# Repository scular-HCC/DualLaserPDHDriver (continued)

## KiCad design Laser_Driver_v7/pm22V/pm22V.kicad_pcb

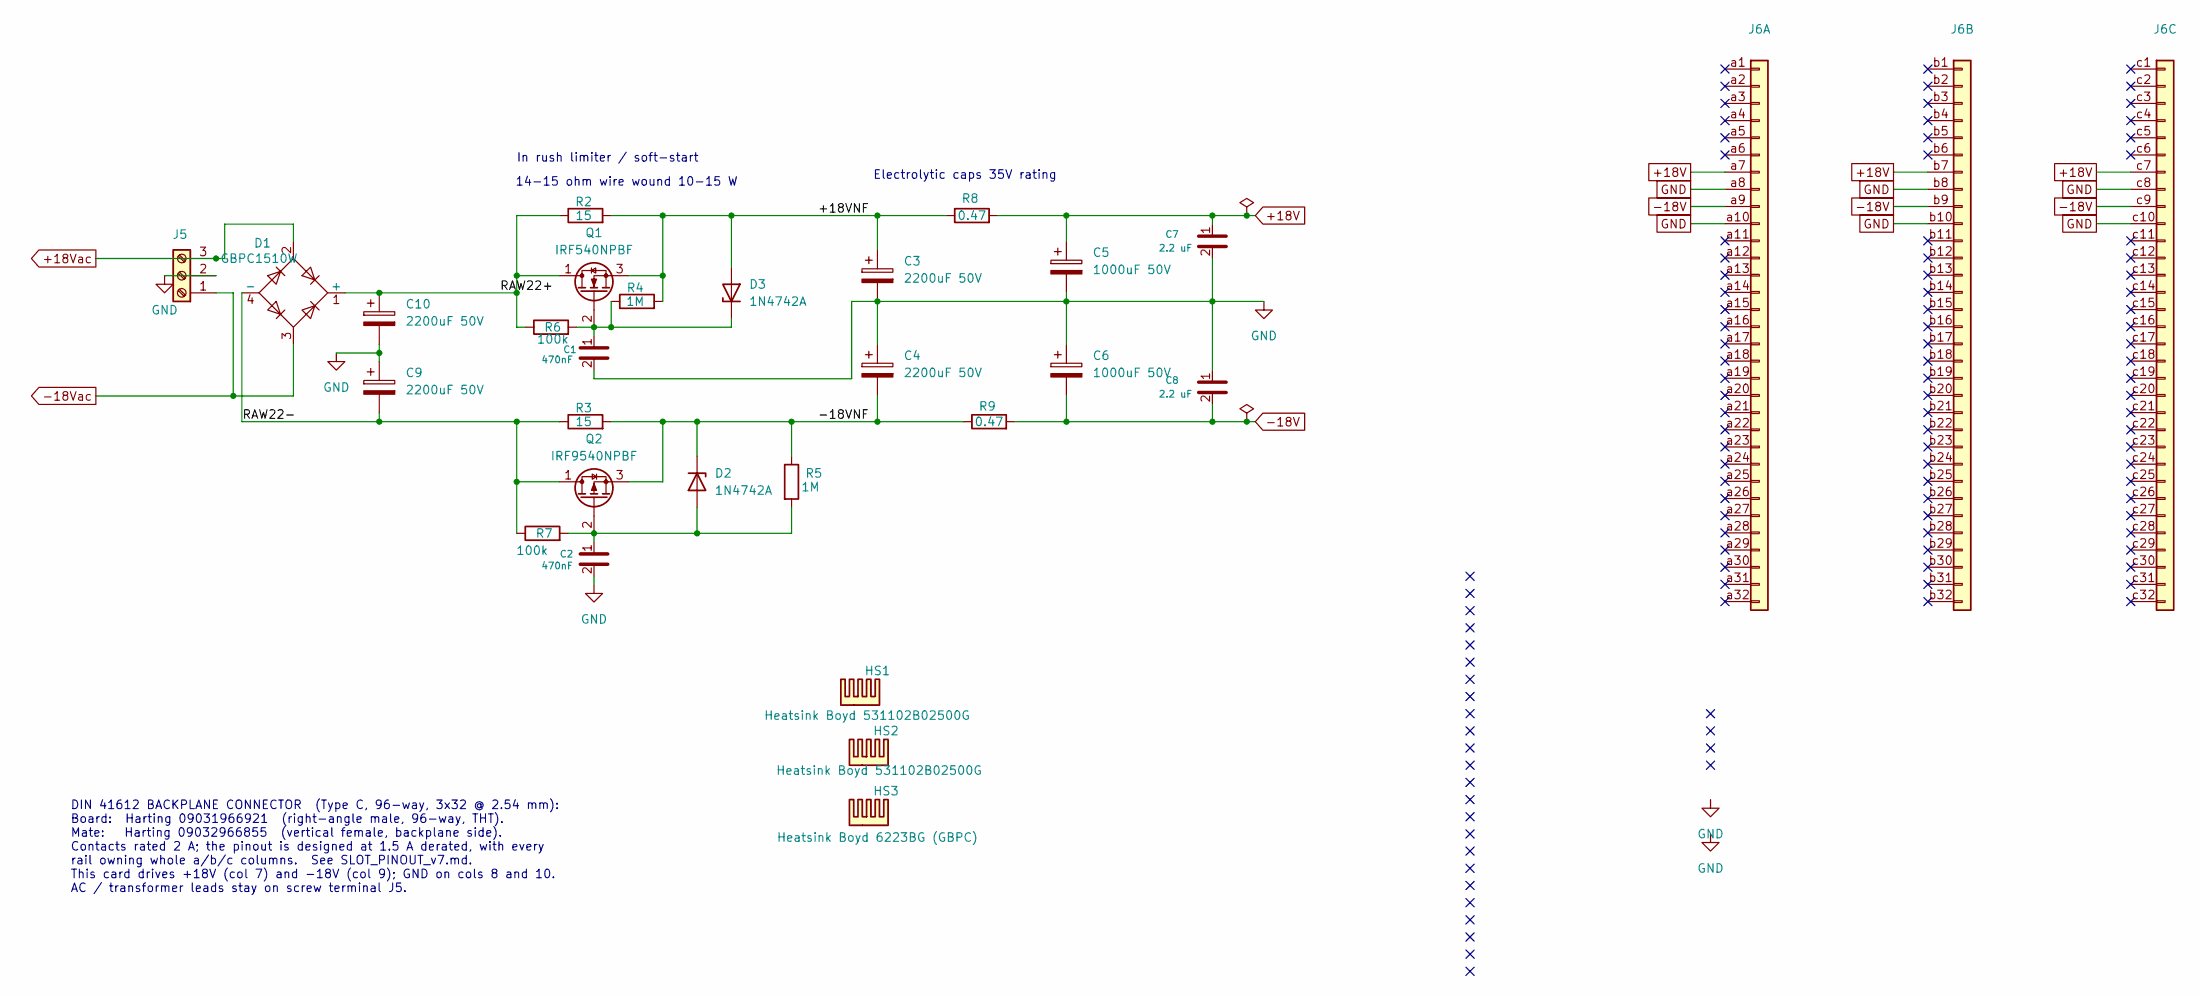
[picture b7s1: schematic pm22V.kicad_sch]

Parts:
C1, C2: 470nF; C_0805_2012Metric_Pad1.18x1.45mm_HandSolder
C3, C4, C9, C10: 2200uF 50V; CP_Radial_D18.0mm_P7.50mm
C5, C6: 1000uF 50V; CP_Radial_D16.0mm_P7.50mm
C7, C8: 2.2 uF; C_0805_2012Metric_Pad1.18x1.45mm_HandSolder
D1: GBPC1510W; Diode_Bridge_28.6x28.6x7.3mm_P18.0mm_P11.6mm; Manufacturer Part Number GBPC1510W; DigiKey P/N 2616-GBPC1510W-ND
D2, D3: 1N4742A; D_DO-41_SOD81_P10.16mm_Horizontal
HS1, HS2: Heatsink Boyd 531102B02500G; Heatsink_AAVID_Extruded_531102B02500G_34.9x12.7mm_H38.1mm
HS3: Heatsink Boyd 6223BG (GBPC); Bridge_GBPC_Heatsink_Boyd_6223BG
J5: Screw_Terminal_01x03; TerminalBlock_Phoenix_MKDS-1,5-3-5.08_1x03_P5.08mm_Horizont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; MPN 1729131
J6: DIN41612_03x32_C_Split; DIN41612_C_3x32_Male_Horizontal_THT
Q1: IRF540NPBF; TO-220-3_Vertical
Q2: IRF9540NPBF; TO-220-3_Vertical
R2, R3: 15; R_Axial_Power_L38.0mm_W9.0mm_P45.72mm
R4, R5: 1M; R_0805_2012Metric_Pad1.20x1.40mm_HandSolder
R6, R7: 100k; R_0805_2012Metric_Pad1.20x1.40mm_HandSolder
R8, R9: 0.47; R_1206_3216Metric_Pad1.30x1.75mm_HandSolder; MPN CRL1206-FW-R470ELF

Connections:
+18V: C5.1, C7.1, J6.a7, J6.b7, J6.c7, R8.2
+18Vac: D1.2, J5.3
-18V: C6.2, C8.2, J6.a9, J6.b9, J6.c9, R9.2
-18Vac: D1.3, J5.1
/+18VNF: C3.1, D3.2 (A), Q1.3 (S), R2.2, R4.2, R8.1
/-18VNF: C4.2, D2.1 (K), Q2.3 (S), R3.2, R5.1, R9.1
/RAW22+: C10.1, D1.1 (+), Q1.1 (D), R2.1, R6.1
/RAW22-: C9.2, D1.4 (-), Q2.1 (D), R3.1, R7.1
GND: C1.2, C2.2, C3.2, C4.1, C5.2, C6.1, C7.2, C8.1, C9.1, C10.2, J5.2, J6.a8, J6.a10, J6.b8, J6.b10, J6.c8, J6.c10
unnamed: C2.1, D2.2 (A), Q2.2 (G), R5.2, R7.2
unnamed: C1.1, D3.1 (K), Q1.2 (G), R4.1, R6.2

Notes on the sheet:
Electrolytic caps 35V rating
DIN 41612 BACKPLANE CONNECTOR (Type C, 96-way, 3x32 @ 2.54 mm): Board: Harting 09031966921 (right-angle male, 96-way, THT). Mate: Harting 09032966855 (vertical female, backplane side). Contacts rated 2 A; the pinout is designed at 1.5 A derated, with every rail owning whole a/b/c columns. See SLOT_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
In rush limiter / soft-start
14-15 ohm wire wound 10-15 W

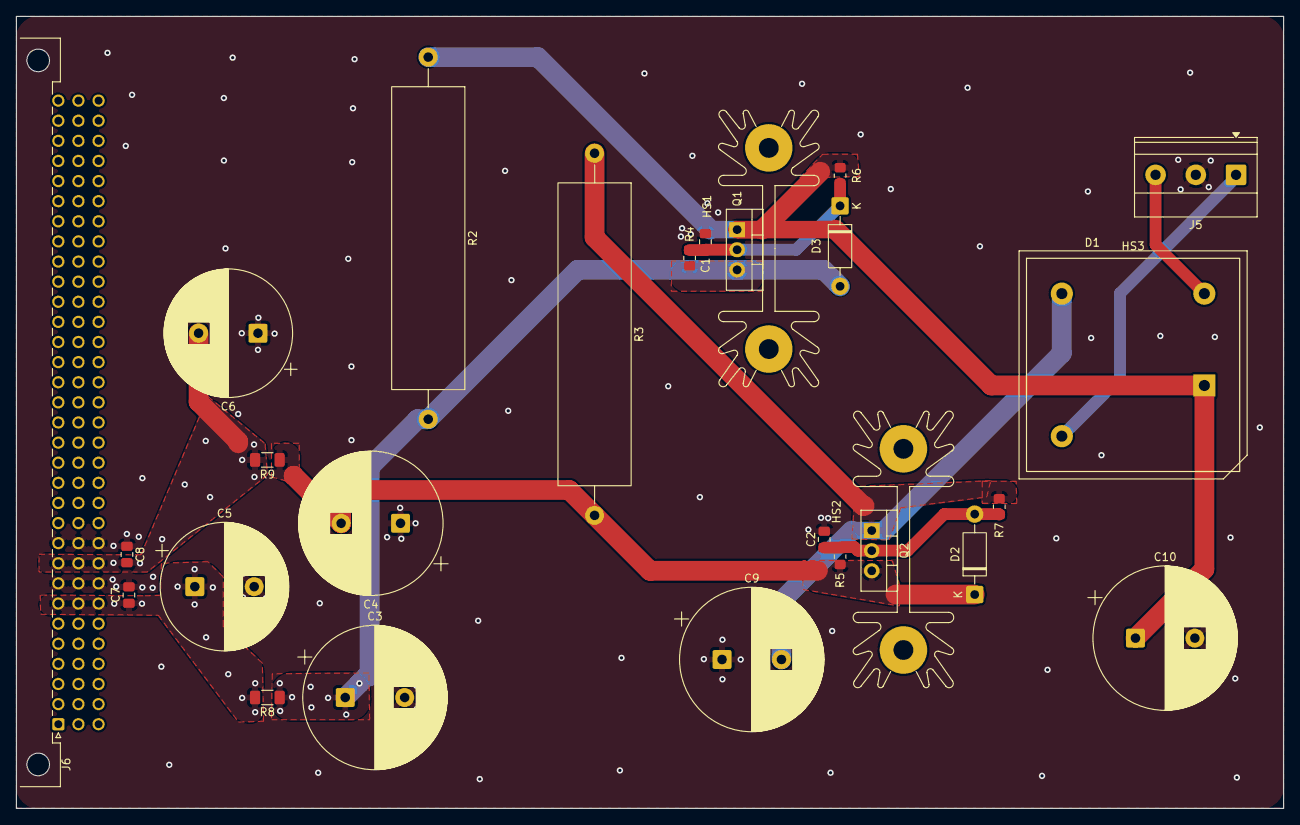
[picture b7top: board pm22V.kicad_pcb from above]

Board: 2 copper layers, 160.0 x 100.0 mm, 28 parts (0 on the bottom side), 11 nets.

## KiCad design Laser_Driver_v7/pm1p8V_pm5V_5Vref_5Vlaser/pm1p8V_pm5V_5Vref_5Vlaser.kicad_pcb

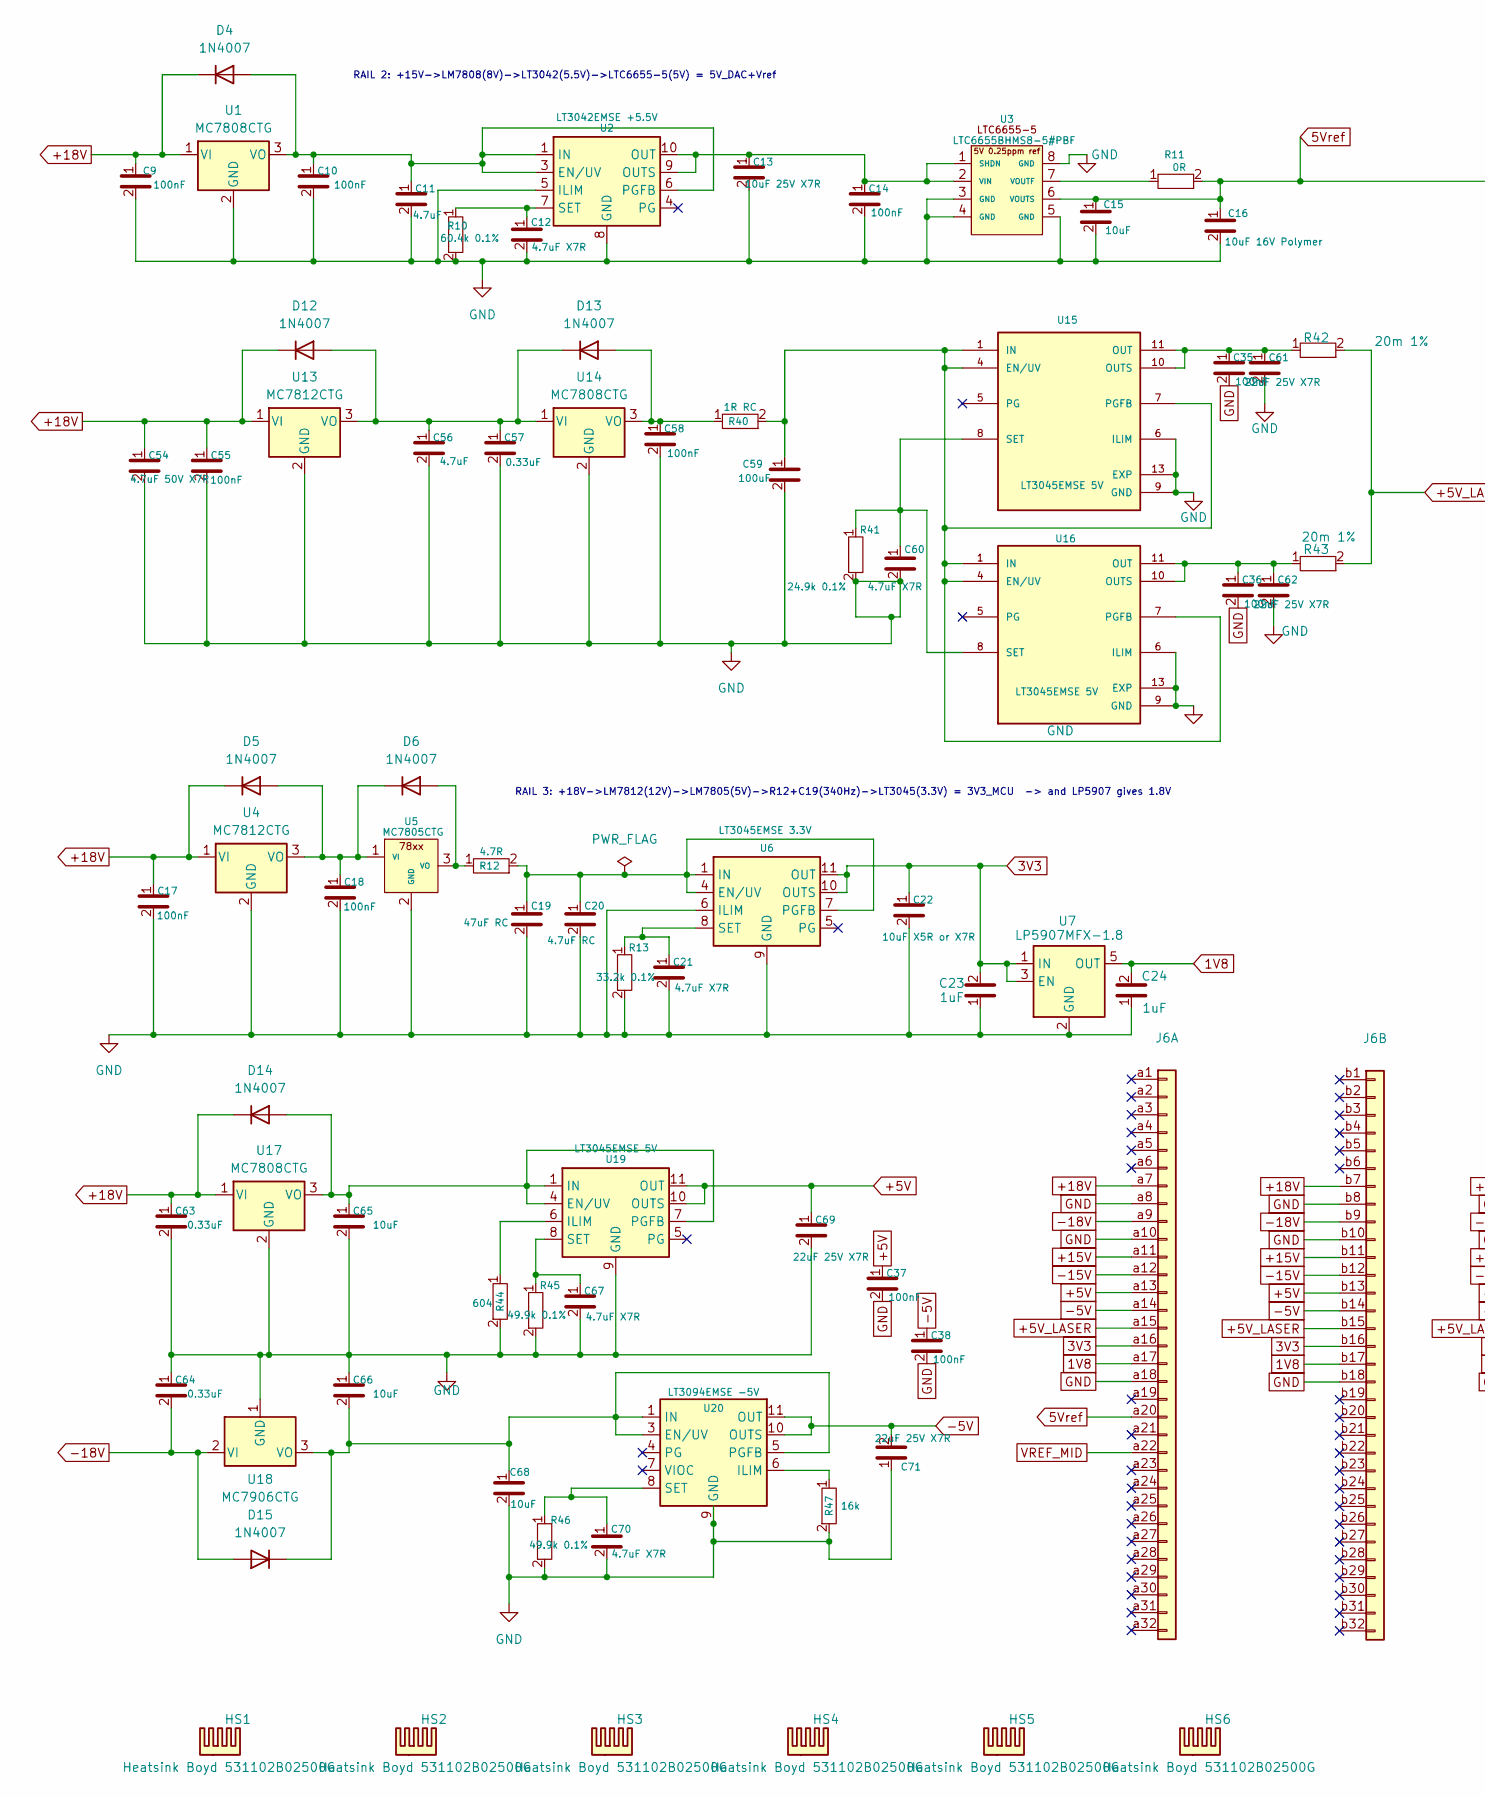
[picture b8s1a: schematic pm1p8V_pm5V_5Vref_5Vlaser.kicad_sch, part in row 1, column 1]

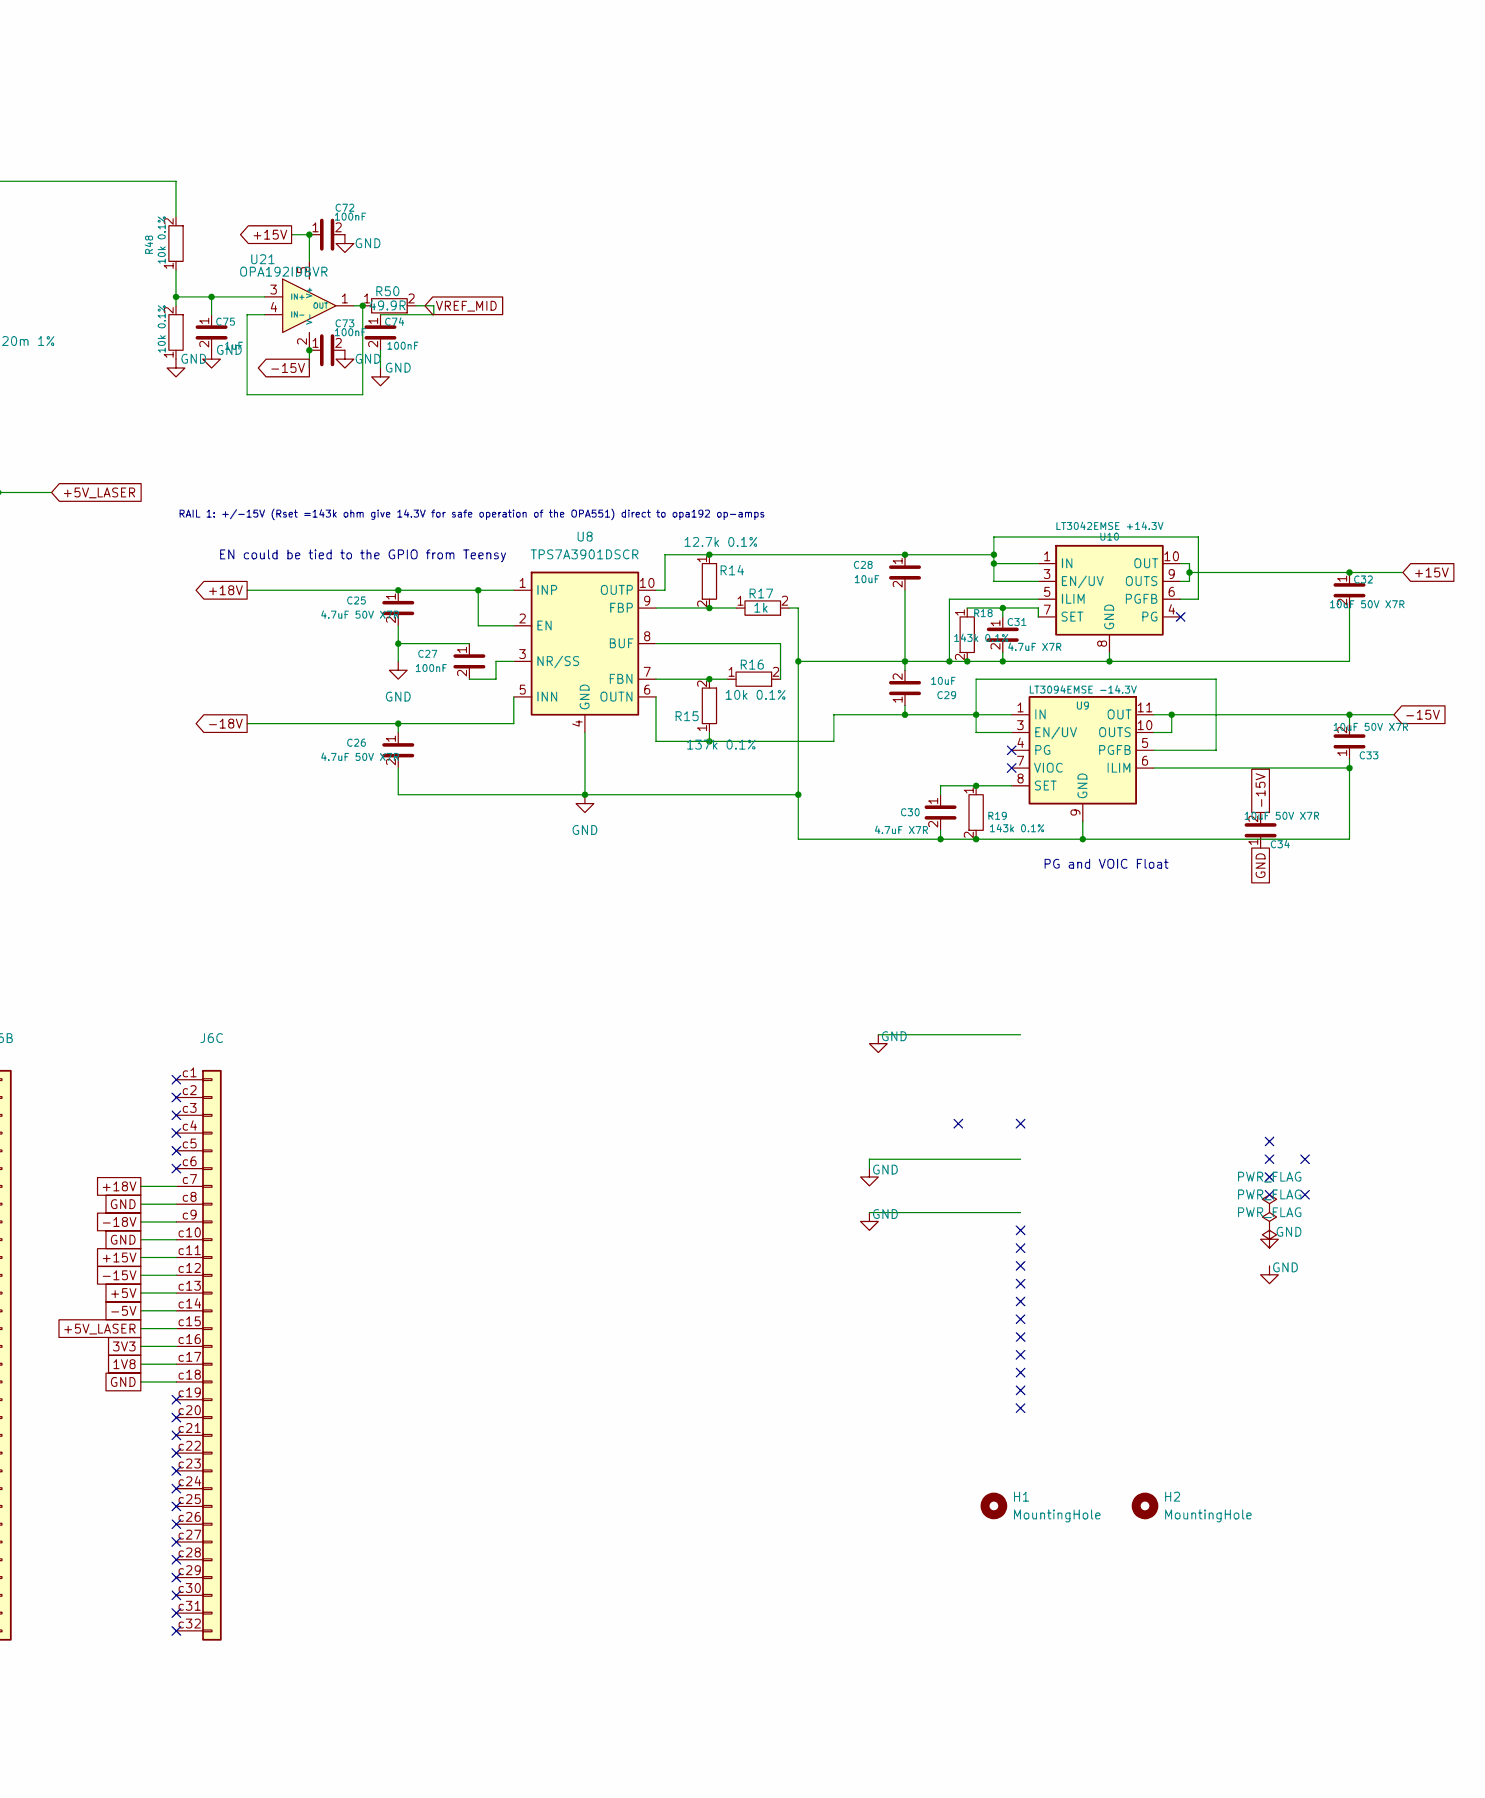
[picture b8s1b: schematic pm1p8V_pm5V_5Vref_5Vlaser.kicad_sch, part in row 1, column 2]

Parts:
C9, C10, C14, C17, C18, C27, C35, C36, C37, C38, C55, C58, C72, C73, C74: 100nF; C_0805_2012Metric_Pad1.18x1.45mm_HandSolder; Manufacturer Part Number CL21B104KBCNNNC; DigiKey P/N 1276-1003-2-ND
C11, C56: 4.7uF; C_0805_2012Metric_Pad1.18x1.45mm_HandSolder; Manufacturer Part Number CL21B475KAFNNNE; DigiKey P/N 1276-2969-2-ND
C12, C21, C30, C31, C60, C67, C70: 4.7uF X7R; C_0805_2012Metric_Pad1.18x1.45mm_HandSolder; Manufacturer Part Number CL21B475KAFNNNE; DigiKey P/N 1276-2969-2-ND
C13: 10uF 25V X7R; C_1206_3216Metric_Pad1.33x1.80mm_HandSolder; Manufacturer Part Number C1206C106K3RACTU; DigiKey P/N 399-C1206C106K3RACTUCT-ND
C15, C28, C29, C65, C66, C68: 10uF; C_0805_2012Metric_Pad1.18x1.45mm_HandSolder; Manufacturer Part Number C0805C106K3PACTU; DigiKey P/N 399-11939-2-ND
C16: 10uF 16V Polymer; CP_EIA-3528-21_Kemet-B_HandSolder; Manufacturer Part Number T520B106M016ATE100; DigiKey P/N 399-5483-2-ND
C19: 47uF RC; C_1210_3225Metric_Pad1.33x2.70mm_HandSolder; Manufacturer Part Number TMK325ABJ476MM-P; DigiKey P/N 587-5479-2-ND
C20: 4.7uF RC; C_0805_2012Metric_Pad1.18x1.45mm_HandSolder; Manufacturer Part Number CL21B475KAFNNNE; DigiKey P/N 1276-2969-2-ND
C22: 10uF X5R or X7R; C_0805_2012Metric_Pad1.18x1.45mm_HandSolder; Manufacturer Part Number C0805C106K3PACTU; DigiKey P/N 399-11939-2-ND
C23, C24: 1uF; C_0805_2012Metric_Pad1.18x1.45mm_HandSolder; Manufacturer Part Number C0805C105K5RACTU; DigiKey P/N 399-C0805C105K5RACTUTR-ND
C25, C26, C54: 4.7uF 50V X7R; C_0805_2012Metric_Pad1.18x1.45mm_HandSolder; Manufacturer Part Number CGA4J1X7R1H475K125AC; DigiKey P/N 445-181404-1-ND
C32, C33, C34: 10uF 50V X7R; C_1210_3225Metric_Pad1.33x2.70mm_HandSolder; Manufacturer Part Number CL32B106KBJNNWE; DigiKey P/N 1276-3388-1-ND
C57, C63, C64: 0.33uF; C_0805_2012Metric_Pad1.18x1.45mm_HandSolder; Manufacturer Part Number CL21B334KBFNNNE; DigiKey P/N 1276-1123-2-ND
C59: 100uF; C_1210_3225Metric_Pad1.33x2.70mm_HandSolder; Manufacturer Part Number 1210YD107MAT2A; DigiKey P/N 478-11408-2-ND
C61, C62, C69, C71: 22uF 25V X7R; C_1210_3225Metric_Pad1.33x2.70mm_HandSolder; Manufacturer Part Number C1210C226M3RACTU; DigiKey P/N 399-C1210C226M3RACTUCT-ND
C75: 1uF; C_0805_2012Metric_Pad1.18x1.45mm_HandSolder; Manufacturer Part Number C0805C105K5RACTU; DigiKey P/N 399-C0805C105K5RACTU-ND
D4, D5, D6, D12, D13, D14, D15: 1N4007; D_DO-41_SOD81_P12.70mm_Horizontal; Manufacturer Part Number 1N4007RLG; DigiKey P/N 1N4007RLGOSTR-ND
H1, H2: MountingHole; MountingHole_2.7mm
HS1, HS2, HS3, HS4, HS5, HS6: Heatsink Boyd 531102B02500G; Heatsink_AAVID_Extruded_531102B02500G_34.9x12.7mm_H38.1mm; Manufacturer Part Number 531102B02500G; DigiKey P/N HS352-ND
J6: DIN41612_03x32_C_Split; DIN41612_C_3x32_Male_Horizontal_THT
R10: 60.4k 0.1%; R_0805_2012Metric_Pad1.20x1.40mm_HandSolder; Manufacturer Part Number ERA-6AEB6042V; DigiKey P/N P60.4KDATR-ND
R11: 0R; R_0805_2012Metric_Pad1.20x1.40mm_HandSolder; Manufacturer Part Number RC0805JR-070RL; DigiKey P/N 311-0.0ARTR-ND
R12: 4.7R; R_1206_3216Metric_Pad1.30x1.75mm_HandSolder; Manufacturer Part Number RC1206FR-074R7L; DigiKey P/N 311-4.70FRTR-ND
R13: 33.2k 0.1%; R_0805_2012Metric_Pad1.20x1.40mm_HandSolder; Manufacturer Part Number ERA-6AEB3322V; DigiKey P/N P33.2KDATR-ND
R14: 12.7k 0.1%; R_0805_2012Metric_Pad1.20x1.40mm_HandSolder; Manufacturer Part Number ERA-6AEB1272V; DigiKey P/N P12.7KDATR-ND
R15: 137k 0.1%; R_0805_2012Metric_Pad1.20x1.40mm_HandSolder; Manufacturer Part Number ERA-6AEB1373V; DigiKey P/N 10-ERA-6AEB1373VTR-ND
R16, R48, R49: 10k 0.1%; R_0805_2012Metric_Pad1.20x1.40mm_HandSolder; Manufacturer Part Number ERA-6AEB103V; DigiKey P/N P10KDATR-ND
R17: 1k; R_0805_2012Metric_Pad1.20x1.40mm_HandSolder; Manufacturer Part Number CRCW08051K00FKEA; DigiKey P/N 541-1.00KCTR-ND
R18, R19: 143k 0.1%; R_0805_2012Metric_Pad1.20x1.40mm_HandSolder; Manufacturer Part Number ERA-6AEB1433V; DigiKey P/N P143KDATR-ND
R40: 1R RC; R_1206_3216Metric_Pad1.30x1.75mm_HandSolder; Manufacturer Part Number RC1206FR-071RL; DigiKey P/N 311-1.00FRTR-ND
R41: 24.9k 0.1%; R_0805_2012Metric_Pad1.20x1.40mm_HandSolder; Manufacturer Part Number ERA-6AEB2492V; DigiKey P/N P24.9KDATR-ND
R42, R43: 20m 1%; R_0805_2012Metric_Pad1.20x1.40mm_HandSolder; Manufacturer Part Number ERJ-6BWFR020V; DigiKey P/N P.02AQTR-ND
R44: 604; R_0805_2012Metric_Pad1.20x1.40mm_HandSolder; Manufacturer Part Number RC0805FR-07604RL; DigiKey P/N 311-604CRTR-ND
R45, R46: 49.9k 0.1%; R_0805_2012Metric_Pad1.20x1.40mm_HandSolder; Manufacturer Part Number ERA-6AEB4992V; DigiKey P/N P49.9KDATR-ND
R47: 16k; R_0805_2012Metric_Pad1.20x1.40mm_HandSolder; Manufacturer Part Number RC0805FR-0716KL; DigiKey P/N 311-16.0KCRTR-ND
R50: 49.9R; R_0805_2012Metric_Pad1.20x1.40mm_HandSolder; Manufacturer Part Number ERJ-6ENF49R9V; DigiKey P/N P49.9CTR-ND
U1, U14, U17: MC7808CTG; TO-220-3_Vertical; Manufacturer Part Number MC7808CTG; DigiKey P/N MC7808CTGOS-ND
U2: LT3042EMSE +5.5V; MSOP-10-1EP_3x3mm_P0.5mm_EP1.68x1.88mm; Manufacturer Part Number LT3042EMSE#PBF; DigiKey P/N 505-LT3042EMSE#PBF-ND
U3: LTC6655BHMS8-5#PBF; MSOP-8_3x3mm_P0.65mm; Manufacturer Part Number LTC6655BHMS8-5#PBF; DigiKey P/N 505-LTC6655BHMS8-5#PBF-ND
U4, U13: MC7812CTG; TO-220-3_Vertical; Manufacturer Part Number MC7812CTG; DigiKey P/N MC7812CTGOS-ND
U5: MC7805CTG; TO-220-3_Vertical; Manufacturer Part Number MC7805CTG; DigiKey P/N MC7805CTGOS-ND
U6: LT3045EMSE 3.3V; MSOP-12-1EP_3x4.039mm_P0.65mm_EP1.651x2.845mm; Manufacturer Part Number LT3045EMSE#PBF; DigiKey P/N 505-LT3045EMSE#PBF-ND
U7: LP5907MFX-1.8; SOT-23-5; Manufacturer Part Number LP5907MFX-1.8/NOPB; DigiKey P/N 296-41463-2-ND
U8: TPS7A3901DSCR; Texas_DSC0010J_ThermalVias; Manufacturer Part Number TPS7A3901DSCR; DigiKey P/N 296-TPS7A3901DSCRTR-ND
U9: LT3094EMSE -14.3V; MSOP-12-1EP_3x4.039mm_P0.65mm_EP1.651x2.845mm; Manufacturer Part Number LT3094EMSE#PBF; DigiKey P/N 505-LT3094EMSE#PBF-ND
U10: LT3042EMSE +14.3V; MSOP-10-1EP_3x3mm_P0.5mm_EP1.68x1.88mm; Manufacturer Part Number LT3042EMSE#PBF; DigiKey P/N 505-LT3042EMSE#PBF-ND
U15, U16: LT3045EMSE 5V; MSOP-12-1EP_3x4.039mm_P0.65mm_EP1.651x2.845mm_ThermalVias; PARTREV D; DigiKey P/N 505-LT3045EMSE#PBF-ND
U18: MC7906CTG; TO-220-3_Vertical; Manufacturer Part Number MC7906CTG; DigiKey P/N MC7906CTGOS-ND
U19: LT3045EMSE 5V; MSOP-12-1EP_3x4.039mm_P0.65mm_EP1.651x2.845mm; Manufacturer Part Number LT3045EMSE#PBF; DigiKey P/N 505-LT3045EMSE#PBF-ND
U20: LT3094EMSE -5V; MSOP-12-1EP_3x4.039mm_P0.65mm_EP1.651x2.845mm; Manufacturer Part Number LT3094EMSE#PBF; DigiKey P/N 505-LT3094EMSE#PBF-ND
U21: OPA192IDBVR; SOT-23-5_HandSoldering; Manufacturer Part Number OPA192IDBVR; DigiKey P/N 296-42105-2-ND

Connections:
1V8: C24.2, J6.a17, J6.b17, J6.c17, U7.5 (OUT)
3V3: C22.1, C23.2, J6.a16, J6.b16, J6.c16, U6.10 (OUTS), U6.11 (OUT), U6.12 (OUT), U7.1 (IN), U7.3 (EN)
5Vref: C15.1, C16.1, J6.a20, R11.2, R48.2, U3.6 (VOUTS)
+5V: C37.1, C69.1, J6.a13, J6.b13, J6.c13, U19.10 (OUTS), U19.11 (OUT), U19.12 (OUT)
+5V_LASER: J6.a15, J6.b15, J6.c15, R42.2, R43.2
+15V: C32.1, C72.1, J6.a11, J6.b11, J6.c11, U10.9 (OUTS), U10.10 (OUT), U21.5 (V+)
+18V: C9.1, C17.1, C25.1, C54.1, C55.1, C63.1, D4.1 (K), D5.1 (K), D12.1 (K), D14.1 (K), J6.a7, J6.b7, J6.c7, U1.1 (VI), U4.1 (VI), U8.1 (INP), U8.2 (EN), U13.1 (VI), U17.1 (VI)
-5V: C38.1, C71.2, J6.a14, J6.b14, J6.c14, U20.10 (OUTS), U20.11 (OUT), U20.12 (OUT)
-15V: C33.2, C34.2, C73.1, J6.a12, J6.b12, J6.c12, U9.10 (OUTS), U9.11 (OUT), U9.12 (OUT), U21.2 (V-)
-18V: C26.1, C64.2, D15.2 (A), J6.a9, J6.b9, J6.c9, U8.5 (INN), U18.2 (VI)
GND: C9.2, C10.2, C11.2, C12.2, C13.2, C14.2, C15.2, C16.2, C17.2, C18.2, C19.2, C20.2, C21.2, C22.2, C23.1, C24.1, C25.2, C26.2, C27.1, C28.2, C29.2, C30.2, C31.2, C32.2, C33.1, C34.1, C35.2, C36.2, C37.2, C38.2, C54.2, C55.2, C56.2, C57.2, C58.2, C59.2, C60.2, C61.2, C62.2, C63.2, C64.1, C65.2, C66.1, C67.2, C68.2, C69.2, C70.2, C71.1, C72.2, C73.2, C74.2, C75.2, J6.a8, J6.a10, J6.a18, J6.b8, J6.b10, J6.b18, J6.c8, J6.c10, J6.c18, R10.2, R13.2, R17.2, R18.2, R19.2, R41.2, R44.2, R45.2, R46.2, R47.2, R49.1, U1.2 (GND), U2.5 (ILIM), U2.8 (GND), U2.11 (GND), U3.3 (GND), U3.4 (GND), U3.5 (GND), U3.8 (GND), U4.2 (GND), U5.2 (GND), U6.6 (ILIM), U6.9 (GND), U6.13 (GND), U7.2 (GND), U8.4 (GND), U8.11 (GND), U9.6 (ILIM), U9.9 (GND), U10.5 (ILIM), U10.8 (GND), U10.11 (GND), U13.2 (GND), U14.2 (GND), U15.6 (ILIM), U15.9 (GND), U15.13 (EXP), U16.6 (ILIM), U16.9 (GND), U16.13 (EXP), U17.2 (GND), U18.1 (GND), U19.9 (GND), U19.13 (GND), U20.9 (GND)
unnamed: C10.1, C11.1, D4.2 (A), U1.3 (VO), U2.1 (IN), U2.2 (IN), U2.3 (EN/UV), U2.6 (PGFB)
unnamed: C18.1, D5.2 (A), D6.1 (K), U4.3 (VO), U5.1 (VI)
unnamed: D6.2 (A), R12.1, U5.3 (VO)
unnamed: C56.1, C57.1, D12.2 (A), D13.1 (K), U13.3 (VO), U14.1 (VI)
unnamed: C58.1, D13.2 (A), R40.1, U14.3 (VO)
unnamed: C65.1, D14.2 (A), U17.3 (VO), U19.1 (IN), U19.2 (IN), U19.3 (IN), U19.4 (EN/UV), U19.7 (PGFB)
unnamed: C66.2, C68.1, D15.1 (K), U18.3 (VO), U20.1 (IN), U20.2 (IN), U20.3 (EN/UV), U20.5 (PGFB), U20.13 (IN)
unnamed: C13.1, C14.1, U2.9 (OUTS), U2.10 (OUT), U3.1 (SHDN), U3.2 (VIN)
unnamed: C12.1, R10.1, U2.7 (SET)
unnamed: R11.1, U3.7 (VOUTF)
unnamed: C19.1, C20.1, R12.2, U6.1 (IN), U6.2 (IN), U6.3 (IN), U6.4 (EN/UV), U6.7 (PGFB)
unnamed: C21.1, R13.1, U6.8 (SET)
unnamed: R16.2, U8.8 (BUF)
unnamed: R15.2, R16.1, U8.7 (FBN)
unnamed: R14.2, R17.1, U8.9 (FBP)
unnamed: C27.2, U8.3 (NR/SS)
unnamed: C29.1, R15.1, U8.6 (OUTN), U9.1 (IN), U9.2 (IN), U9.3 (EN/UV), U9.5 (PGFB), U9.13 (IN)
unnamed: C30.1, R19.1, U9.8 (SET)
unnamed: C28.1, R14.1, U8.10 (OUTP), U10.1 (IN), U10.2 (IN), U10.3 (EN/UV), U10.6 (PGFB)
unnamed: C31.1, R18.1, U10.7 (SET)
unnamed: C59.1, R40.2, U15.1 (IN), U15.2 (IN), U15.3 (IN), U15.4 (EN/UV), U15.7 (PGFB), U16.1 (IN), U16.2 (IN), U16.3 (IN), U16.4 (EN/UV), U16.7 (PGFB)
unnamed: C35.1, C61.1, R42.1, U15.10 (OUTS), U15.11 (OUT), U15.12 (OUT)
unnamed: C60.1, R41.1, U15.8 (SET), U16.8 (SET)
unnamed: C36.1, C62.1, R43.1, U16.10 (OUTS), U16.11 (OUT), U16.12 (OUT)
unnamed: R44.1, U19.6 (ILIM)
unnamed: C67.1, R45.1, U19.8 (SET)
unnamed: R47.1, U20.6 (ILIM)
unnamed: C70.1, R46.1, U20.8 (SET)
unnamed: C75.1, R48.1, R49.2, U21.3 (IN+)
unnamed: R50.1, U21.1 (OUT), U21.4 (IN-)
VREF_MID: C74.1, J6.a22, R50.2

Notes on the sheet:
EN could be tied to the GPIO from Teensy
PG and VOIC Float
RAIL 3: +18V->LM7812(12V)->LM7805(5V)->R12+C19(340Hz)->LT3045(3.3V) = 3V3_MCU -> and LP5907 gives 1.8V
RAIL 1: +/-15V (Rset =143k ohm give 14.3V for safe operation of the OPA551) direct to opa192 op-amps
RAIL 2: +15V->LM7808(8V)->LT3042(5.5V)->LTC6655-5(5V) = 5V_DAC+Vref

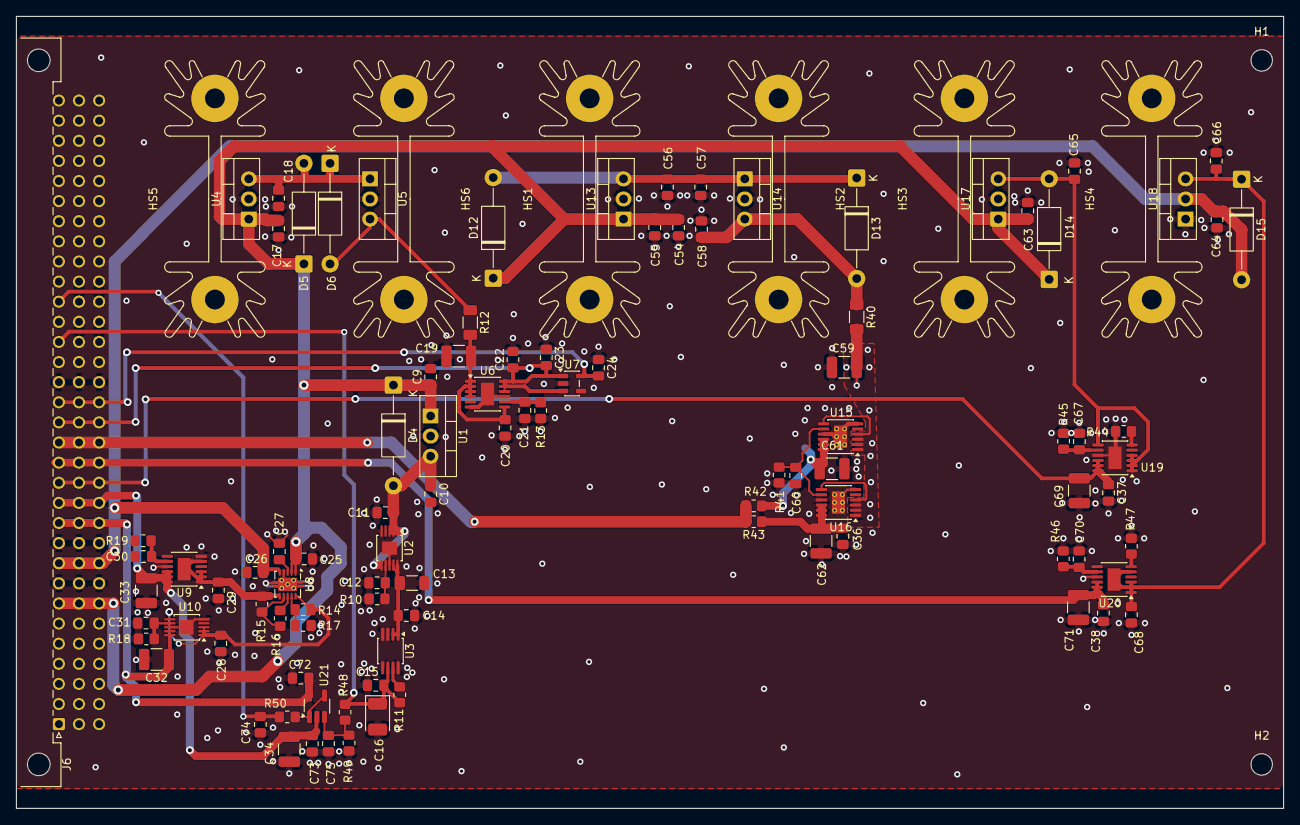
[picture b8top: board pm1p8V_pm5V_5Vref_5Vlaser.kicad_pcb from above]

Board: 2 copper layers, 160.0 x 100.0 mm, 108 parts (1 on the bottom side), 42 nets.

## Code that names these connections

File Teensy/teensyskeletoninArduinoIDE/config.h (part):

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// --- Shared fault line (open-drain wired-OR, active-low) ----
// Any card may assert; source identified via that card's PCA9538.
// External 10k pullup R305 on the DIG card; internal pullup as backup.
#define PIN_FAULT_N       31   // was HBRIDGE_FAULT1

// ============================================================
// I2C address map (7-bit) — from the ONE CH-card address jumper:
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#define I2C_ADS1115_AFE      0x4A          // AFE card (ADDR -> SDA)
#define I2C_AD5696_CH1       0x0C          // base 0x0C | GA0
#define I2C_AD5696_CH2       0x0D
#define I2C_AD5696_AFE       0x0E          // AFE ERR offset-null DAC (A1=1, A0=0)
#define I2C_PCA9538_CH1      0x70          // base 0x70 | GA0  (A1 tied to GND)
#define I2C_PCA9538_CH2      0x71

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#define PIN_MISO          12

// AD9833 DDS chips
#define PIN_AD9833_1_CS    2    // DDS1_FSYNC — CH1 DRIVE (Ω, to bias-tee injection)
#define PIN_AD9833_2_CS    3    // DDS2_FSYNC — CH2 DRIVE (Ω)
#define PIN_AD9833_1_RESET 4
#define PIN_AD9833_2_RESET 5
// Reference DDS (Option B): phase-set demod LO, one per channel.
// All four AD9833 share the one 25 MHz MCLK → drive/reference phase-coherent.
#define PIN_AD9833_3_CS    6    // DDS3_FSYNC — CH1 REFERENCE (demod LO → LO1_REF)
#define PIN_AD9833_4_CS    8    // DDS4_FSYNC — CH2 REFERENCE (demod LO → LO2_REF)

// Analog PI integrator hold/run (lock enable) — one per channel.
// v5: no longer a Teensy GPIO. Driven via each CH card's PCA9538 IO0
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
// --- SPI1 (display) — MOSI=26, MISO=39, SCK=27 -------------
// All five TFT signals are on adjacent pins for clean PCB routing.
#define PIN_TFT_MOSI      26   // SPI1 MOSI
#define PIN_TFT_SCK       27   // SPI1 SCK
#define PIN_TFT_CS        28
#define PIN_TFT_DC        29   // data/command select — required
#define PIN_TFT_RST       30
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// the per-card ADS1115s — read via chcard_poll()/afe_poll(). Only the
// fast post-mix baseband error stays on the Teensy ADC (ERRn_BUS,
// backplane c13/c14):
#define PIN_LOCK1_IN      A10  // pin 24 — CH1 baseband error (ERR1_BUS)
#define PIN_LOCK2_IN      A11  // pin 25 — CH2 baseband error (ERR2_BUS)
// DIG card conditioning (traced from DIG_Card.kicad_sch, rev C as fabbed):
//   ERRn_BUS -> R303/R304 3k3 series -> ERRn_ADC -> A10/A11,
//   with C303/C304 1n to GND and a BAT54S (D301/D302) clamping the ADC
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// clip point, so the existing lock/acquire thresholds keep their
// meaning and stay symmetric.  adc_to_error() clamps to +/-1.
// ============================================================
#define ERR_CENTER_V      2.5f            // VREF_MID (buffered 5Vref/2, pm1p8V U21)
#define ERR_MID_COUNTS    (ERR_CENTER_V / ADC_REF_V * ADC_MAX)          // ~3102
#define ERR_SPAN_COUNTS   ((ADC_REF_V - ERR_CENTER_V) / ADC_REF_V * ADC_MAX)  // ~993
#define ERR_GAIN_VV       5.02f           // AFE R138/(R116+R118) = 49.9k/9.95k (inverting);
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// Monitor-photodiode optical power (CH card rev C).
// The DFB1550LP internal PD (anode J_BTF1.3→GND, cathode J_BTF1.4→
// MPD_K) sinks I_pd from the MPD_K node; that current is drawn through
// R_bias1 from U_TIA2's virtual ground, which is pinned at NTC_A. So
// U_TIA1 buffers MPD_MON = NTC_A − I_pd·R_bias1, and the NTC_A offset
// must be SUBTRACTED OUT to recover the photocurrent:
//   I_pd  = (NTC_A − MPD_MON) / R_bias1
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// ============================================================
#define MPD_R_BIAS_OHM        20000.0f  // R_bias1 (Ω)
#define MPD_RESP_UA_PER_MW    2.2f      // PD monitor responsivity
#define MPD_MW_PER_V          22.7f     // (NTC_A − MPD_MON) volts → mW

// ============================================================
// Laser IMON scaling — matches CH card rev C hardware:
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// Hardware: INA828 (G = 1 + 50k/8.06k = 7.20 exactly), shunt R=0.1Ω
// (was INA826, G=7.13; the 0.72 V/A constant is now exact)
//   V_IMON = TEC_IMON_OFFSET_V + TEC_IMON_V_PER_A * I_amps
//   At 0 A  → ~1.20 V  (INA828 REF pin, from TEC_VZERO buffer)
//   At 2.5 A → ~3.00 V  (Vmax from schematic annotation)
// DAC zero-current code for the ≈1.20V virtual-zero. v5: AD5696R with
// internal 2.5V ref × gain 2 → 5V span, so the code is unchanged from
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// ============================================================
// H-Bridge / card faults — v5: the OPA551 Flag lands on each CH
// card's PCA9538 IO1; the expander's ~INT drives the shared FAULT_n
// line (PIN_FAULT_N above).
//
// rev D: IO1 is ACTIVE-HIGH. The Flag pin is a current SOURCE (<50 nA
// healthy, 80 uA min in thermal shutdown) into R49 33k to GND, with D23
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
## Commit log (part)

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2026-05-25 Power supplies past first check
    General design for power supply complete. Need to go through models and footprints for all components.
2026-05-26 More updates for the power supply
    H-bridge for TEC making sense. +/-6V supply now making sense with capacitor multiplier good for 3A per polarity.
2026-05-27 Added more spec sheets.
2026-05-27 Updated 5Vref and TEC and TEC controller
2026-05-27 Worked on completing Controls and Drivers and CLK.
    Laser and TEC drivers and controls now mostly complete. Added a Clock that runs off an internal 10 MHz or switches to external 10 MHz. Made minor changes elsewhere.
2026-05-27 Added DFB package sheet with pinout. Minor update
2026-05-28 First full draft complete. Added Teensy pinout sheet.
    Used Copilot to generate firmware draft. ** Still need to: Recheck all specifications and pins, verify design with simulations, go through all footprints, create layout.
2026-05-28 Ran Teensy 4.1 code through copilot. Added ILI9341.
    Teensy code compiles without error now.
2026-05-29 Renumbered schematics, corrections, power verified
2026-05-29 Update names, footprints, values, and created BOM
    Updated files names, foot prints, component values, parts.
    Assigned values from Digikey catalog.
    Created CSV BOMs for each schematic.
    Including a Power analysis now for all components.
2026-05-29 first placement of all components on pcb.
2026-05-29 PCB layout report first iteration
2026-05-29 Added to display.
2026-05-29 Clearing ERC errors. laying out components.
2026-05-30 Teensy code modular and interface and display
    Major changes to the Teensy code to make it easier to understand and maintain. It is now split across multiple files based on the logical functions. Added ethernet support and a webpage to control/mo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
2026-05-31 Added demo mode and edit ethernet settings.
    Added demo mode, edit ethernet settings. Updated documentation.
2026-06-01 Added display to schematic. Updated BOM.
2026-06-01 Update to teensy pinout and config. Working on PCB
    Improved pin selection on Teensy for better operation.
    Started working through the PCB from in the power input.
    Updating footprints and getting the layout organized.
2026-06-01 Working through power supply layout and footprints
2026-06-02 Began routing.
2026-06-03 Added separate xfrmer for 6V.
    Added inrush protection with NTC and increased capacitance to reduce ripple on 6V
2026-06-03 Changed xfrmers, paralled BJTs for cap multiplier
    Changed the transformers to more appropriate voltages.
    Made the BJTs for the cap multipliers in parallel to better handle the load.
    Simulated the output ripple for the 6V.
    Clarifying notes, removed LT1028 changed to OPA192 to match circuit as drawn.
    Changed divider values for the TEC_zero value to be 1.2 V as designed.
2026-06-03 Many changes. Working through ERC.
    Main changes are for the grounds. I found the NETTIE function to tie the GND, DGND and AGND together at a specific point on the boud with a footprint even.
    Changed transformers one more time to be consistent for both.
    Updated footprints to be consistent and avoid power input/output errors with the ERC.
2026-06-03 Added software limit to TEC current, Hbridge Fault
    Software limit to TEC current. Monitors up to 2.5 A, then flags and reduces setting.
    Hbridge fault now wired to Teensy and software flags.
2026-06-03 Updated documentation for current limite and fault
2026-06-04 6 V supply. Annotations. Teensy zero current.
2026-06-04 Update documentation and Teensy Sketch -demo issue
2026-06-04 Uncertainty budget for IMod vs RFMod.
    Uncertainty budget for current modulation (current design) vs rf modulation was made in jupyter notebook.
2026-06-04 Update UCertBudget for Colab
2026-06-04 Added fractional uncertainty.
    One on the carrier frequency and one on 20GHz sensor range.
2026-06-04 Improved uncertainty budget for ratiometric
2026-06-05 Changed to an RF modulation
    Based on the uncertainty calculation, needed to change from a low frequency modulation to an RF modulation. This drive down the noise, but required a very different implentation. The modulation is li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
2026-06-05 Updated the RF modulation implementation.
2026-06-05 BOM and Project Summary created.
2026-06-07 Split into a power and signal board.
    I think all footprints are now valid. Need to figure out the power connections between boards, currently just screw terminals for wire. I think a single multi-pin connector will work, but want to fin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
2026-06-08 First power pcb layout without traces.
2026-06-09 Changed layout to create hot and cool zones.
2026-06-10 Started working on routing.
2026-06-10 Updated LT3045 footprints started Cu pours
2026-06-10 Power PCB lay out done with no DRC errors.
2026-06-12 updated to newer/available parts
    Routing needs to be completely redone.
2026-06-14 Fixed board after update and crash
2026-06-14 Update zeners to LM4051 SOT-23
2026-06-15 Added NTC for heatsink. orrected screw terminal#s
2026-06-15 Updated Digikey availability
2026-06-17 Adding rail voltage good led circuitry.
2026-06-17 Started placing voltage monitor parts.
2026-06-18 Switching to Eurocard layouts.
    First iteration on first card. Still need to define the pins for the backplane connector.
2026-06-19 Corrected card dimension now need to replace
2026-06-22 Power board all parts placed need to look at therm
2026-06-26 version 5 further split power 22 V and 6 V 2-pcbs
2026-06-30 v5 ac board and pm22V board ready
